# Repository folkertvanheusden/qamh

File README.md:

qamh
----

NOTE: do not use older than version 0.3!

NOTE: THE NOTCH OF THE POWERCONNECTOR (only the notch) IS ON THE WRONG SIDE!!!

Due to the unavailability for a long time already of the Grains module, I decided to recreate the device.
This repo contains the Kicad schematics and PCB design.
It is not a literal conversion: some features were added and the layout is different.

This device is an Eurorack/Doepfer-A100 modulair-synthesizer module. It allows you to upload your own firmware and then produce whatever effect you want it to do.

I found a modification on the web where someone put a piezo on pin 6 of the Arduino (Nano), for that I added a header (GND + D6).

I did *not* look at the original PCB, only at the documentation I found on the web ( https://www.thonk.co.uk/shop/ginkosynthese-grains-full-diy-kit/ ).

The design should be compatible with the original Grains module and should be able to run the original software without modifications.

This design is released under the CC0 license, but do with it whatever you want.

Clone this repo using "--recurse-submodules" as it contains submodules.

Please note: this is work in progress. At the point of writing this (October 7, 2023) the design was not tested.

Modifications:
* D2 can be connected to a button
* D6 can be connected to a piezo buzzer

Folkert van Heusden <mail@vanheusden.com>

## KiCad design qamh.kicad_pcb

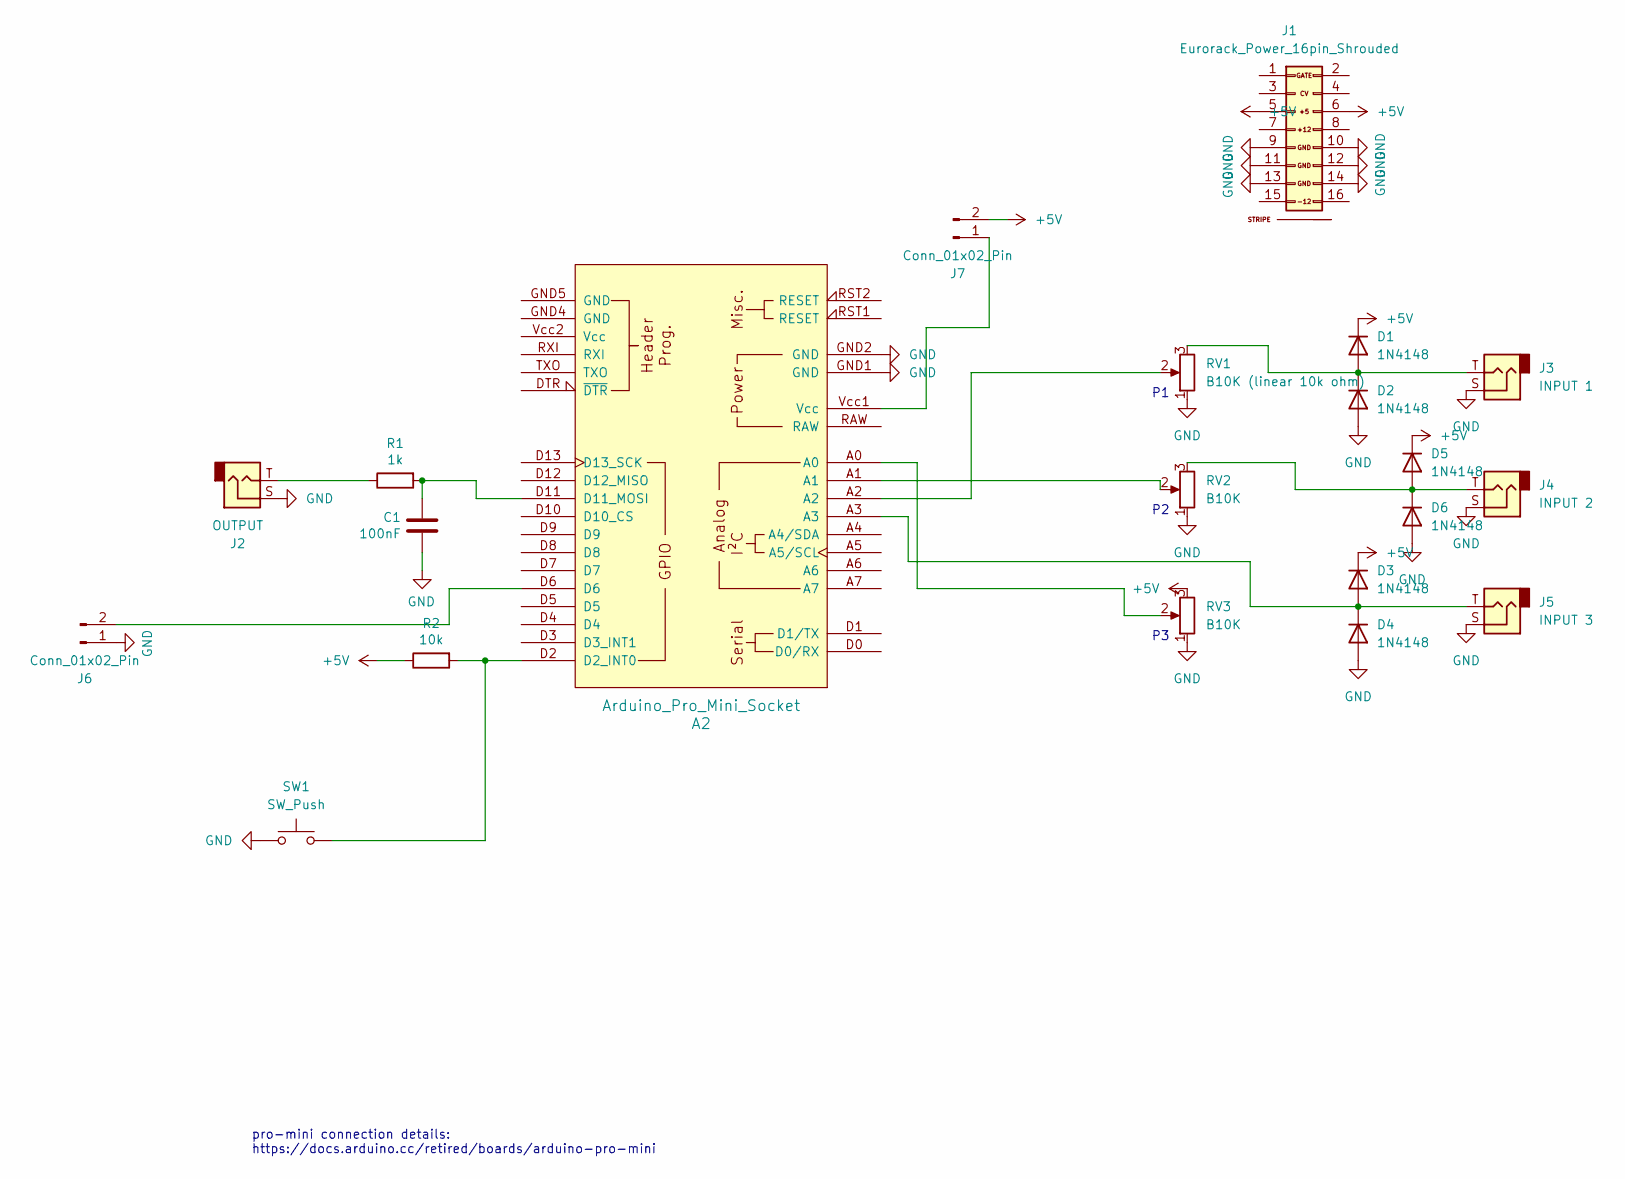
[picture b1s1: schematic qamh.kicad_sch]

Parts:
A2: Arduino_Pro_Mini_Socket
C1: 100nF; C_Disc_D5.0mm_W2.5mm_P5.00mm
D1, D2, D3, D4, D5, D6: 1N4148; D_DO-35_SOD27_P7.62mm_Horizontal
J1: Eurorack_Power_16pin_Shrouded; Pins_2x08_2.54mm_TH_EuroPower_Shrouded; Part Number LL1007-1 (2*8 HITEMP)
J2: OUTPUT; Jack_3.5mm_QingPu_WQP-PJ398SM_Vertical_CircularHoles
J3: INPUT 1; Jack_3.5mm_QingPu_WQP-PJ398SM_Vertical_CircularHoles
J4: INPUT 2; Jack_3.5mm_QingPu_WQP-PJ398SM_Vertical_CircularHoles
J5: INPUT 3; Jack_3.5mm_QingPu_WQP-PJ398SM_Vertical_CircularHoles
J6, J7: Conn_01x02_Pin; PinHeader_1x02_P2.54mm_Vertical
R1: 1k; R_Axial_DIN0204_L3.6mm_D1.6mm_P7.62mm_Horizontal
R2: 10k; R_Axial_DIN0204_L3.6mm_D1.6mm_P7.62mm_Horizontal
RV1: B10K (linear 10k ohm); Potentiometer_Alps_RK09K_Single_Vertical
RV2, RV3: B10K; Potentiometer_Alps_RK09K_Single_Vertical
SW1: SW_Push; SW_PUSH_6mm_H5mm

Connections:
+5V: D1.1 (K), D3.1 (K), D5.1 (K), J1.5 (+12V), J1.6, J7.2, R2.1, RV3.3
GND: A2.GND1 (GND), A2.GND2 (GND), C1.2, D2.2 (A), D4.2 (A), D6.2 (A), J1.9 (GND), J1.10 (GND), J1.11 (GND), J1.12 (GND), J1.13 (-12), J1.14 (-12V), J2.S, J3.S, J4.S, J5.S, J6.1, RV1.1, RV2.1, RV3.1, SW1.1
unnamed: A2.D2 (D2_INT0), R2.2, SW1.2
unnamed: A2.D11 (D11_MOSI), C1.1, R1.2
unnamed: A2.A0, RV3.2
unnamed: A2.A1, RV2.2
unnamed: A2.A2, RV1.2
unnamed: D1.2 (A), D2.1 (K), J3.T, RV1.3
unnamed: A2.A3, D3.2 (A), D4.1 (K), J5.T
unnamed: D5.2 (A), D6.1 (K), J4.T, RV2.3
unnamed: J2.T, R1.1
unnamed: A2.D6, J6.2
unnamed: A2.Vcc1 (Vcc), J7.1

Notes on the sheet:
pro-mini connection details: https://docs.arduino.cc/retired/boards/arduino-pro-mini

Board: 2 copper layers, 21 parts (10 on the bottom side), 13 nets, no tracks yet.

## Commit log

2023-10-06 fix (2) pot
2023-10-07 power needs to be fed via the vin of the nano
2023-10-07 libraries
2023-10-07 logo's, header for piezo
2023-10-07 readme
2023-10-07 pics
2023-10-07 Create LICENSE
2023-10-07 license
2023-10-07 potmeters are B10k (linear 10k ohm)
2023-10-07 will be rebuild by kicad
2023-10-07 meta data in sheet
2023-10-07 git meta
2023-10-08 meta
2023-10-08 replaced nano by pro mini
2023-10-08 arduino pro-mini layout
2023-10-08 pro mini in readme
2023-10-08 nano
2023-10-09 routing
2023-10-09 added button to D2
2023-10-10 header for plug/unplug 5V
2023-10-11 hardware test
2023-10-11 audible test-signal on pin 11
2023-10-11 better test sound
